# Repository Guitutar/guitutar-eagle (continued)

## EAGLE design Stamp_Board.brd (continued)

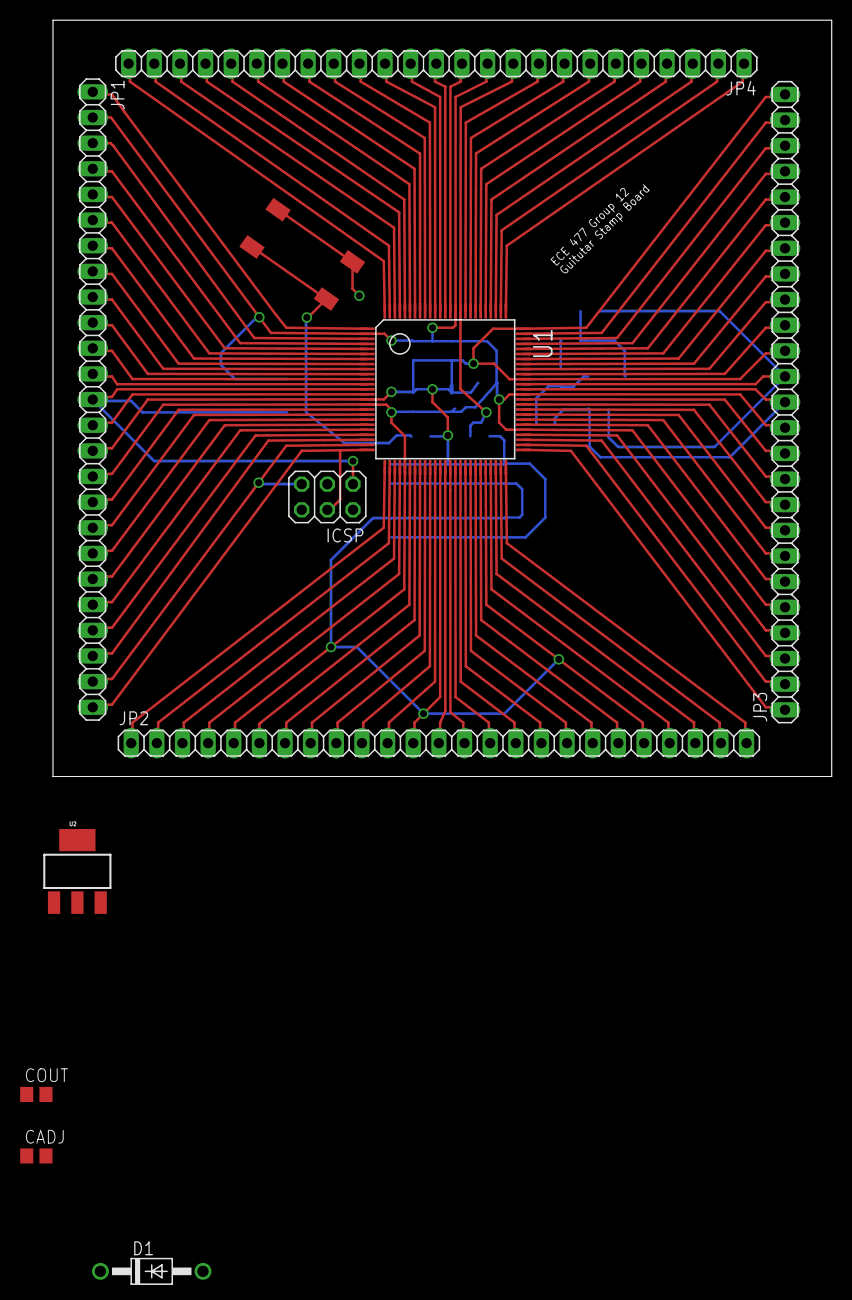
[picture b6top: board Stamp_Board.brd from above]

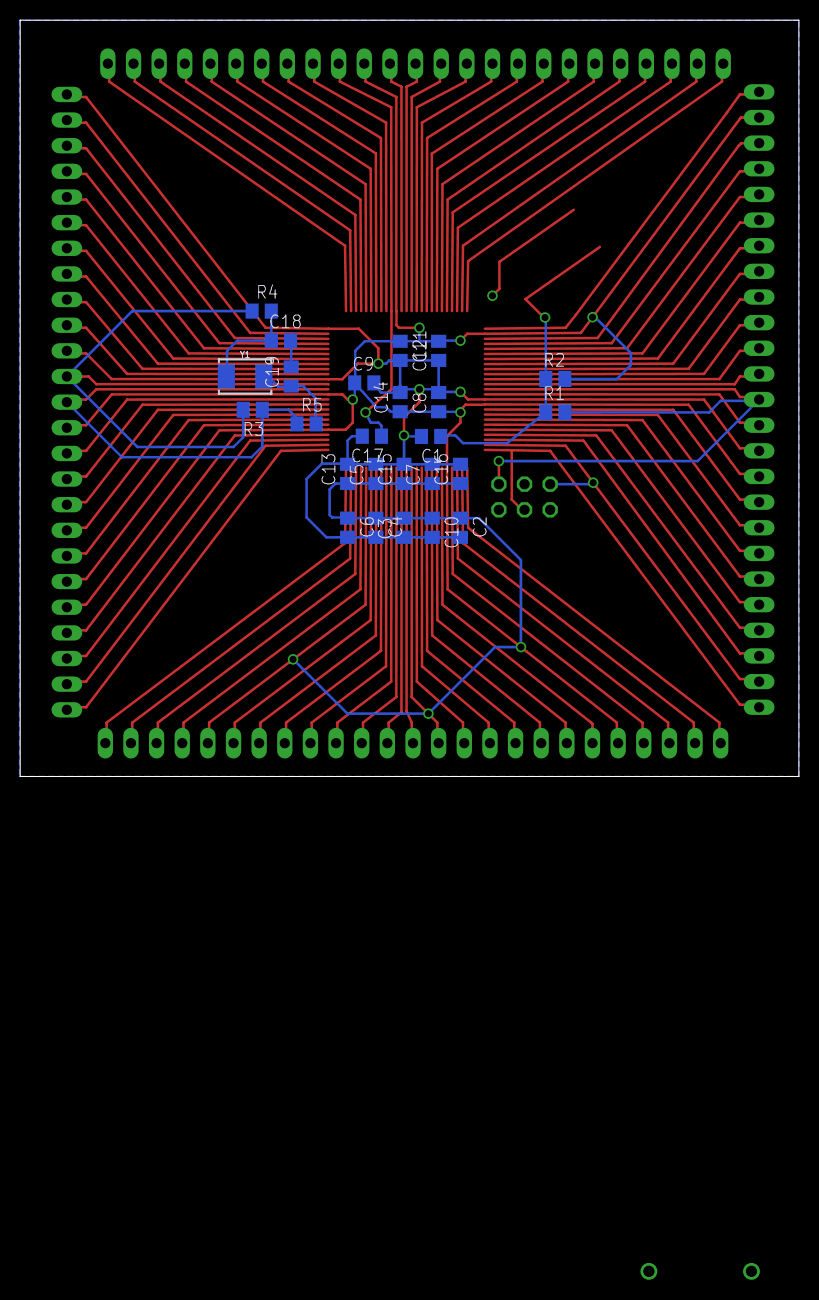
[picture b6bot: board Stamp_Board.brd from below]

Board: 2 copper layers, 77.1 x 74.9 mm, 36 parts (25 on the bottom side), 92 nets.

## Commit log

2017-02-15 Removed temporary files from accidental commit
2017-02-15 Preventing accidental temp adds
2017-02-15 Added basic README
2017-02-15 Moved part slightly as demo
2017-02-17 Added headers, Bluetooth, ICSP header, and I/O connections
2017-02-17 Added xref connections, switch matrix, and connected all MCU pins to headers
2017-02-17 Updating Guitutar.lbr and adding Adafruit PowerBoost files. Committing LED schematic
2017-02-17 Updated Bluetooth module to BM78SPPS5
2017-02-17 Added LEDs and connected them to MCU. Increased size of page 2.
2017-02-21 Created new schematic of just the stamp board and made layout for the schematic.
2017-02-24 Adding Stamp board schematic and board layout. Updated SR name labels and updated LED array.
2017-02-24 Added series resistors to prevent overvoltage/overcurrent.
2017-02-27 updated schematic to include oscillator, resistor packages, and split main schematic into the five PCBs that we will need. Also started the PCB3 layout that includes the microcontroller.
2017-02-27 Finished the remaining component traces for PCB3 layout, but not the traces to other boards
2017-03-01 Added oscillator schematic to Stamp Board and started layout corrections.
2017-03-01 Completed stamp board layout
2017-03-01 Changed most pins on micro and condensed all of the connections on PCB3. Began making traces for other PCBs from PCB3 and created GRN plane for PCB3.
2017-03-03 Added pads for frets, redid traces from micro to other PCBs
2017-03-06 Updated stamp board with reset button and oscillator.
2017-03-06 Finished routing traces for both sides of micro
2017-03-07 Completed traces to other PCBs
2017-03-08 Added more caps because of PIC32 recommended connection. Updated and finished PCB layout. Added LDO to regulate input voltage.
2017-03-08 Updated Bluetooth module from SPP05 to SPPS5.
2017-03-08 Started PCB1 layout. Added pads for fret. Updated BT module to SPPS5.
2017-03-08 Progress on PCB1 layout. Added solder jumpers to schematic.
2017-03-10 Added jumper part to library
2017-03-11 Finished PCB1, PCB3, and added parts to ECE477 library
2017-03-11 Added pin AMP to micro for amplifier circuit
2017-03-24 Added ESD protection resistors on PCB1_new
2017-03-29 PCB2 for remote work
2017-03-30 Finished changing dimensions for PCB3 and switched out resistors for smaller ones.
2017-03-30 Finished changes to PCB1 by switching out resistor packages and reordering the pin connections for PCB2
2017-04-02 Moved resistor and fret pad on PCB1_new
2017-04-03 Modifying dimensions on PCB#_new boards
2017-04-04 Updated ref des to match those in BOM
2017-04-05 Fixed pin distances for PCB2 and added shift register pins to the right side of board
2017-04-05 Finished PCB3 checks and added traces for shift registers
2017-04-06 Moved traces around. Added another hole for AMP input
2017-04-06 Moved traces around. DRC check done
2017-04-06 Fixed library issue where library won't load. Added jumpers and resistor arrays to PCB4
2017-04-07 Finished PCB4. Finished gerbers for PCB1, 2, 3, and 4
